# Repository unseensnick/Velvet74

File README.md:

# Velvet74

A 74-key split keyboard with Choc switches and a chip-down RP2040 on each half, in the Sofle layout. Key positions,
the board outline and the case come from [Ergogen](https://github.com/ergogen/ergogen); parts, nets and
fabrication data live in a KiCad 10 project aimed at JLCPCB assembly.

## The board

One 4-layer board, 268 x 118 mm before the panel rails, holds both halves 10 mm apart. Each half has 37 keys: a 6 x 5 matrix, 5 thumb
keys and 2 EC11 encoders that double as keys, each with an SK6812MINI-E under it.

- **Controller (per half):** RP2040, W25Q128JV 16 MB QSPI flash, 12 MHz ABM8-272-T3 crystal, AP2112K-3.3 LDO,
  BOOTSEL and RESET buttons.
- **USB-C host port:** 1.1 A polyfuse, B5819W reverse-current diode into +5V, SMF5.0A TVS on VBUS, USBLC6-2P6 on
  the data pair.
- **USB-C link port:** joins the halves (+5V, ground and a one-wire link on GP12), protected by its own USBLC6-2P6.
- **Display:** a 0.91" SSD1306 module on the 4-pin J3 header (I2C1).
- **Stackup:** signals on F.Cu and B.Cu, the +5V plane on In1 (with a +3.3V island under the controller), GND on
  In2. Power runs through the planes.
- **Panel:** the halves ship as one 268 x 131 mm panel. A 5 mm rail above and below carries the 2 mm tooling holes
  and three fiducials, and ten 5 mm tabs hold the halves, five per half, away from the USB-C cutouts. Mouse bites
  perforate each tab at the board edge: snap the tabs, then file the nubs flat. Nothing is left on the keyboard.

The schematic draws one half (`velvet74-half.kicad_sch`) and uses it twice, as sheets `Left` and `Right`.
Left references are plain (U1, SW10); right ones add 200 (U201, SW210). Both halves share one pin map.

## Pin map (both halves)

| Function | Pins |
| --- | --- |
| Rows 1-5, thumb row | GP5, GP4, GP3, GP2, GP1, GP0 |
| Columns outer to inner | GP29, GP28, GP27, GP26, GP25, GP24 |
| Encoder 1 (SW16) | A GP13, B GP14, key column GP20 |
| Encoder 2 (SW65) | A GP18, B GP19 |
| Display I2C1 | SDA GP6, SCL GP7 |
| RGB data | GP10, through the U6 level shifter to 5 V |
| Split link | GP12 |
| VBUS sense | GP9 (10k/10k divider) |
| Handedness jumper JP1 | GP8 (3.3 V = left, GND = right) |

37 LEDs at full white exceed the USB budget, so firmware should cap RGB brightness (around 120 of 255).

## Layout

- `velvet74.kicad_pro` / `.kicad_sch` / `.kicad_pcb` / `.kicad_dru`: the KiCad project, with the half sheet
  above.
- `lib/`: project symbols, footprints and 3D models (`my-soffle.*`), and the used JLCPCB library parts (`jlcpcb/`).
- `datasheets/`: manufacturer datasheets for every part on the board, synced from LCSC.
- `ergogen/`: the live layout (`config.yaml`). `npm run build` writes both halves' points, outline and case to
  `ergogen/output/`.
- `scripts/`: KiCad Python scripts that place parts from the Ergogen points and snap LEDs, diodes and caps to their
  switches.
- `templates/rp2040-inner-column/`: the RP2040 module the controller block started from, with its own README.
- `production/`: fabrication outputs, regenerated from the board before an order. `jlcpcb/` holds the
  Fabrication Toolkit set; `pcbway/` holds a `kicad-cli` set with a manufacturer-part-number BOM and assembly
  drawings. The two placement files use different rotation conventions, so do not mix them (see
  `production/pcbway/README.md`).

`CLAUDE.md` has the detailed file map, the rules for editing the design safely, and the checks.

## Getting started

**To open, review or edit the design** you need only [KiCad 10](https://www.kicad.org/download/) (made with
10.0.3); open `velvet74.kicad_pro`. Every library part the design uses is in the repo: the project's own parts
in `lib/my-soffle.*`, and the JLCPCB parts it uses in `lib/jlcpcb/` (copied from the JLCPCB library, MIT). The
remaining parts and 3D models are KiCad's stock ones. No Plugin and Content Manager packages, environment variables
or library setup are needed, and the 3D viewer shows every part. KiCad 8 cannot open these files; tag
`kicad8-final` is the last KiCad 8 state.

**To regenerate the layout** (key positions, outline, case): [Node.js](https://nodejs.org/) 18 or newer (Ergogen's `mathjs` dependency
requires it), then

```bash
cd ergogen && npm install && npm run build
```

Ergogen 4.2.1 is pinned in `ergogen/package.json`; the output lands in `ergogen/output/`.

**To run the scripts in `scripts/`:** KiCad's bundled Python (`<KiCad>/10.0/bin/python.exe` on Windows), with KiCad
closed. Each script's docstring says how to run it and what it overwrites.

**To regenerate `production/jlcpcb/`:** the Fabrication Toolkit plugin (from the KiCad Plugin and Content
Manager), with its automatic translation left **off**. JLCPCB's zero degrees is the part's orientation in its own
LCSC package drawing, which differs from KiCad's for some packages, so each affected part carries an
`FT Rotation Offset` or `FT Position Offset` field checked against JLC's own footprint. The plugin's name-matching
rules would rotate parts that are already right.

**To regenerate `production/pcbway/`:** `scripts/export_pcbway.py`, which drives `kicad-cli` and then writes the
placement file and an MPN-keyed BOM. Those offset fields are JLCPCB's and must not be applied here, so the
placement file keeps KiCad's own angles; the only correction is moving the four USB-C rows onto the part centroid.

**To commit:** activate the tracked commit-message hook once per clone with `git config core.hooksPath .githooks`
(see `CLAUDE.md` for the message format).

## Checks

```bash
kicad-cli sch erc --severity-error --exit-code-violations velvet74.kicad_sch
kicad-cli pcb drc --schematic-parity --severity-error --exit-code-violations velvet74.kicad_pcb
```

Expected: ERC has no errors. DRC has 26 known `courtyards_overlap` errors (mounting holes H1-H5 against their
neighbouring switches, 13 per half) and no unconnected items or parity issues. With all severities shown there are
also known warnings: 24 ERC `pin_to_pin` warnings and 3 `lib_symbol_mismatch` (J201, J202 and JP201 differ from their
library copies), and DRC silkscreen and `lib_footprint_mismatch` warnings for parts edited on the board.

## License

The design files, scripts and documentation are released under the MIT license (see `LICENSE`): you may use,
modify, build and sell them as long as the copyright notice is kept. The design comes with no warranty; check it
yourself before ordering boards.

Credits and third-party parts:

- The layout follows the [Sofle keyboard](https://github.com/josefadamcik/SofleKeyboard) by Josef Adamcik
  (MIT, (c) 2019 Josef Adamcik).
- `lib/jlcpcb/` holds parts of [CDFER/JLCPCB-Kicad-Library](https://github.com/CDFER/JLCPCB-Kicad-Library)
  (MIT, (c) 2024 Chris Dirks, license in `lib/jlcpcb/LICENSE`).
- `lib/my-soffle.3dshapes/SW_Hotswap_Kailh_Choc_V1.wrl` and the Choc hotswap footprints derive from
  [kiswitch/keyswitch-kicad-library](https://github.com/kiswitch/keyswitch-kicad-library) (MIT and CC-BY-SA 4.0).
- `datasheets/` holds the manufacturers' datasheets. They are the manufacturers' copyright, included for reference
  only, and are not covered by this project's license.

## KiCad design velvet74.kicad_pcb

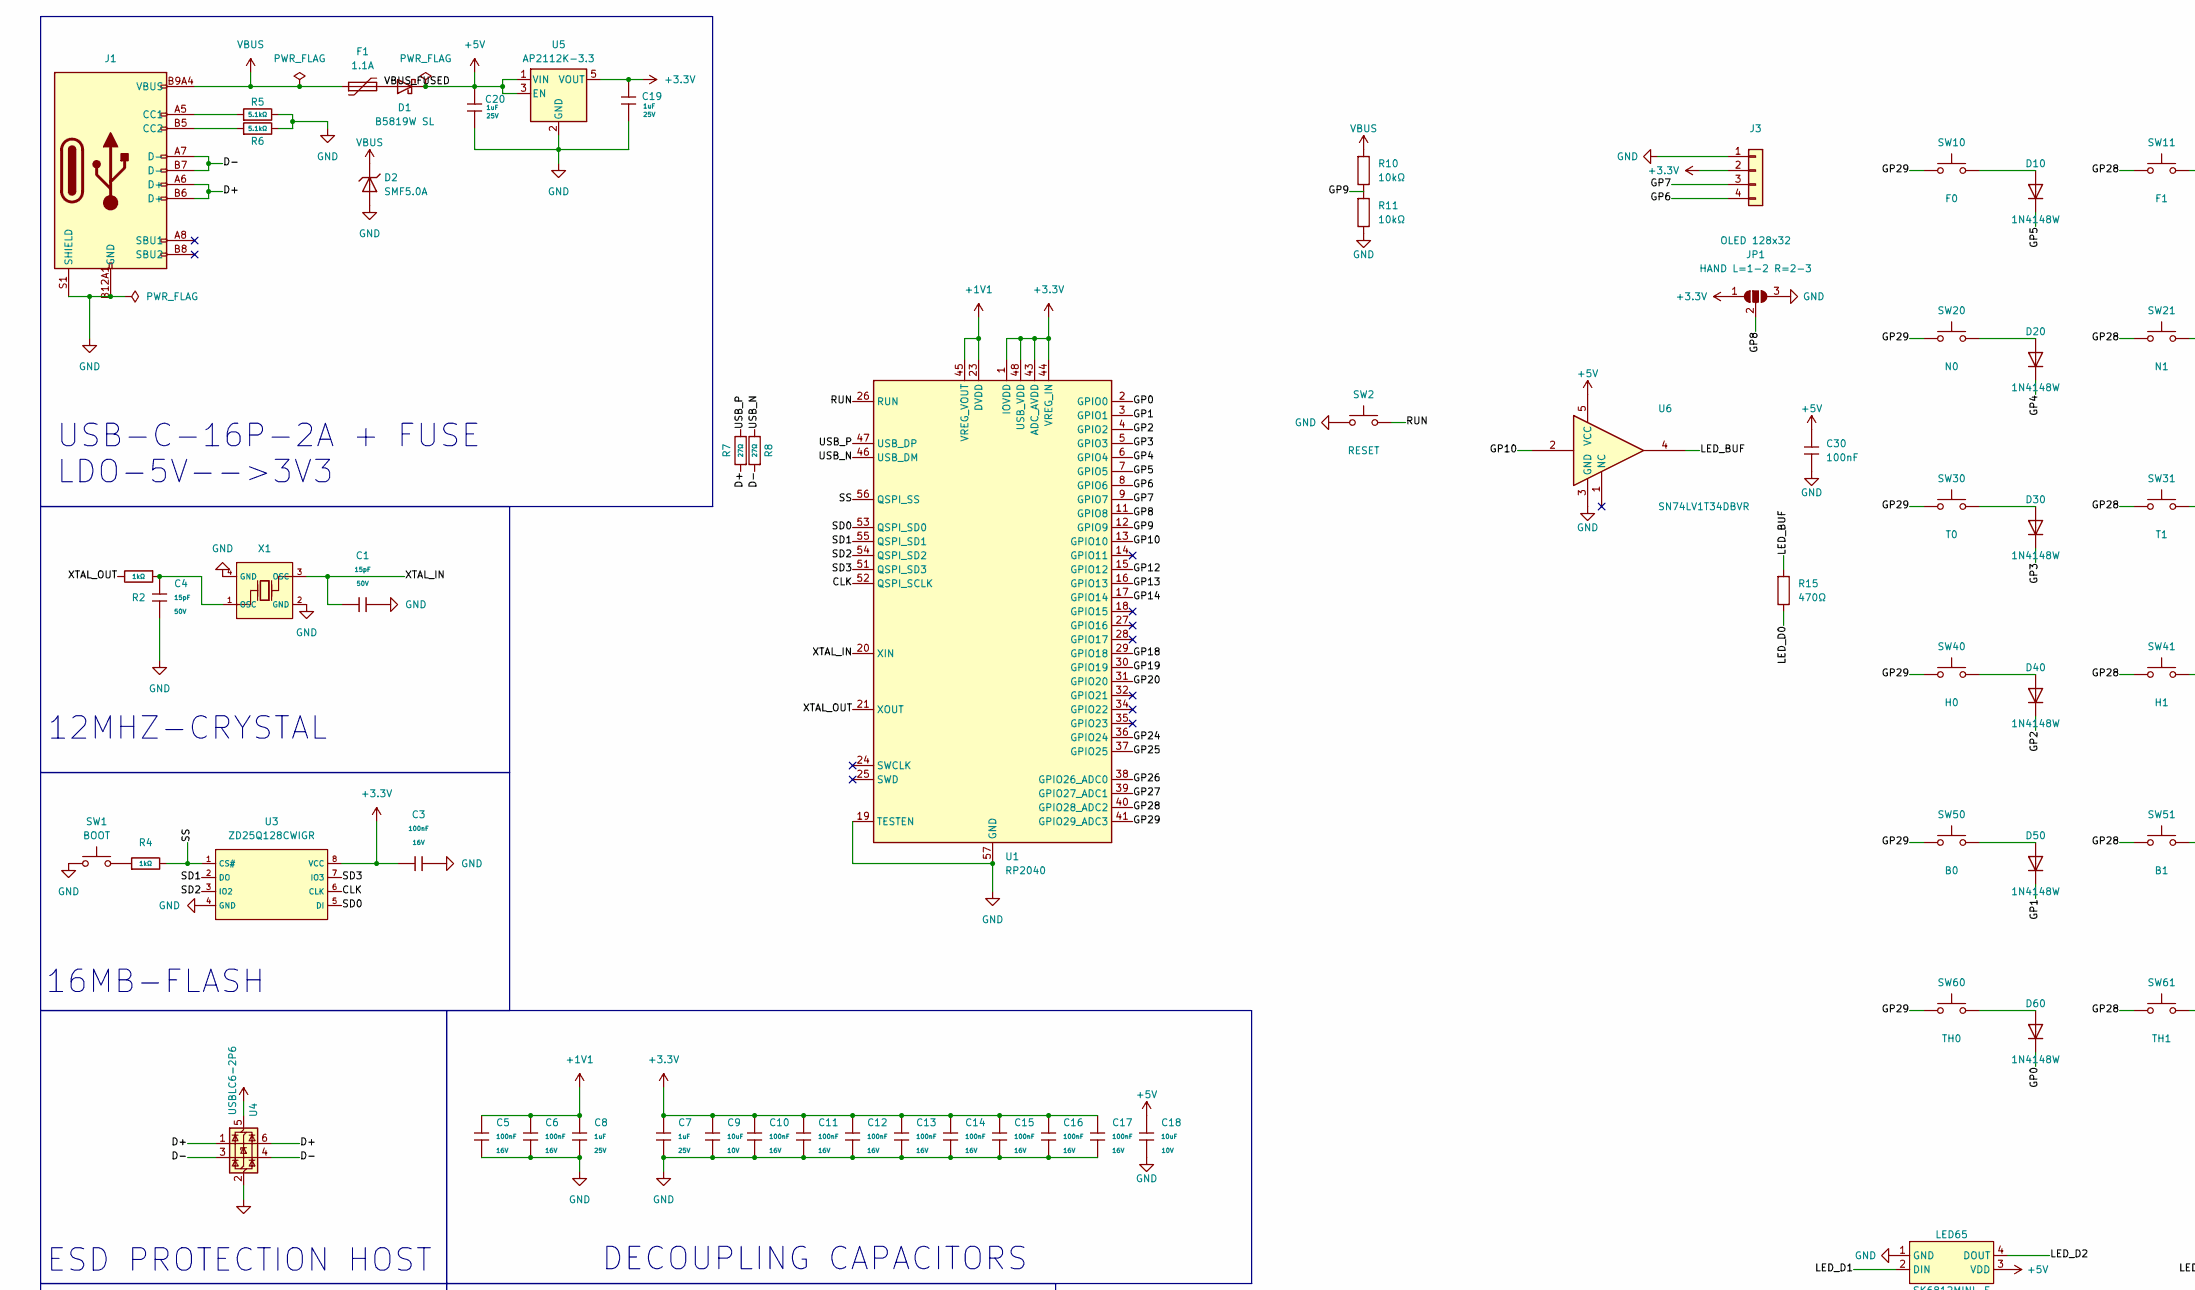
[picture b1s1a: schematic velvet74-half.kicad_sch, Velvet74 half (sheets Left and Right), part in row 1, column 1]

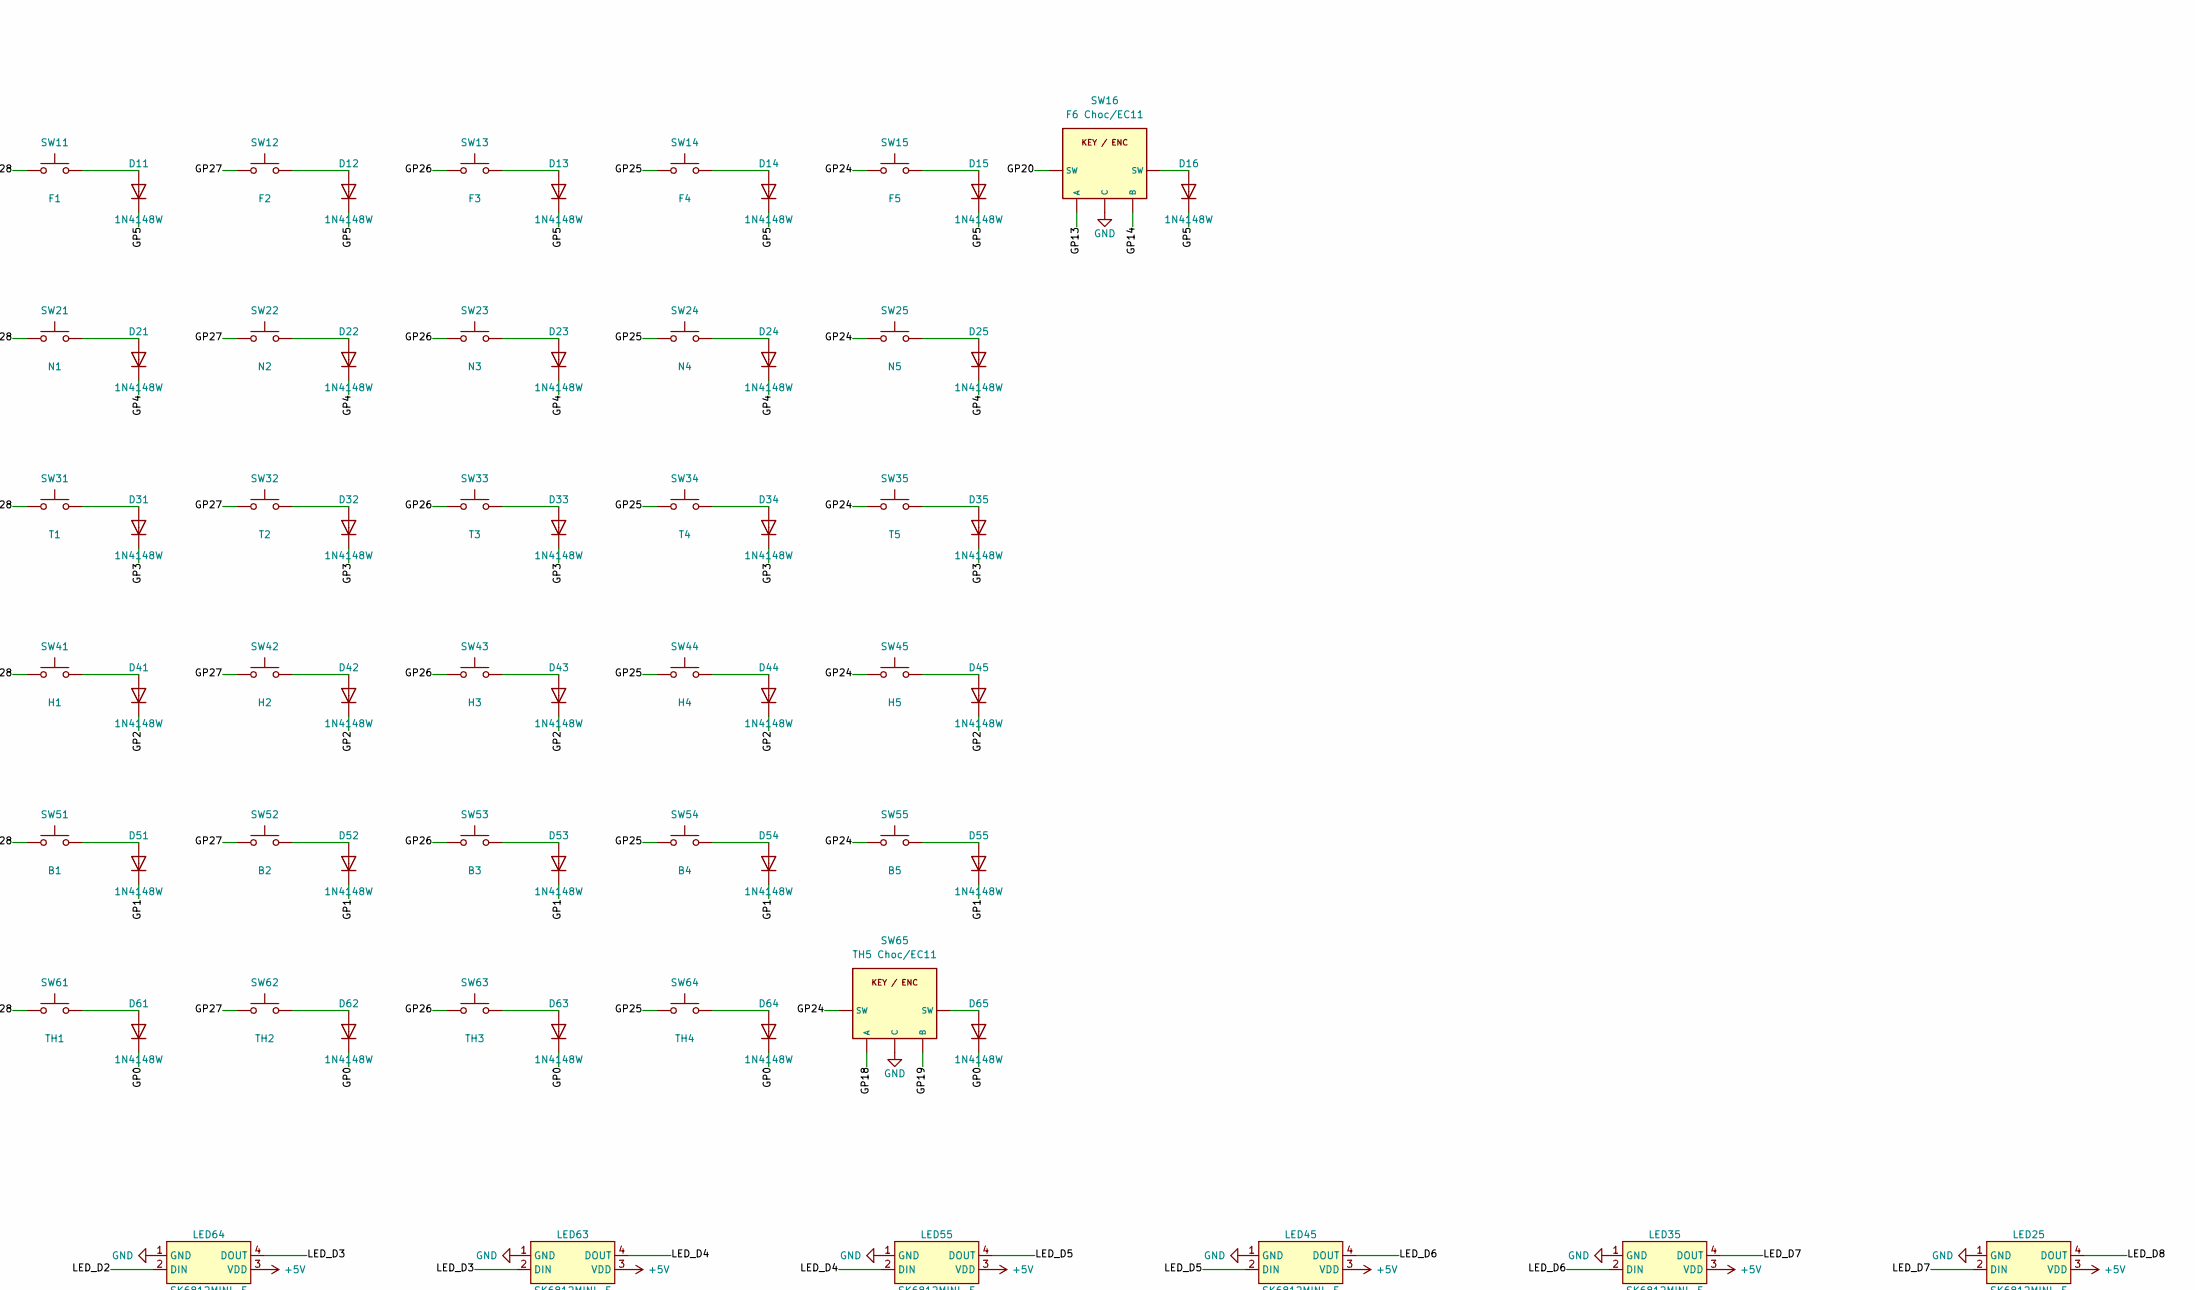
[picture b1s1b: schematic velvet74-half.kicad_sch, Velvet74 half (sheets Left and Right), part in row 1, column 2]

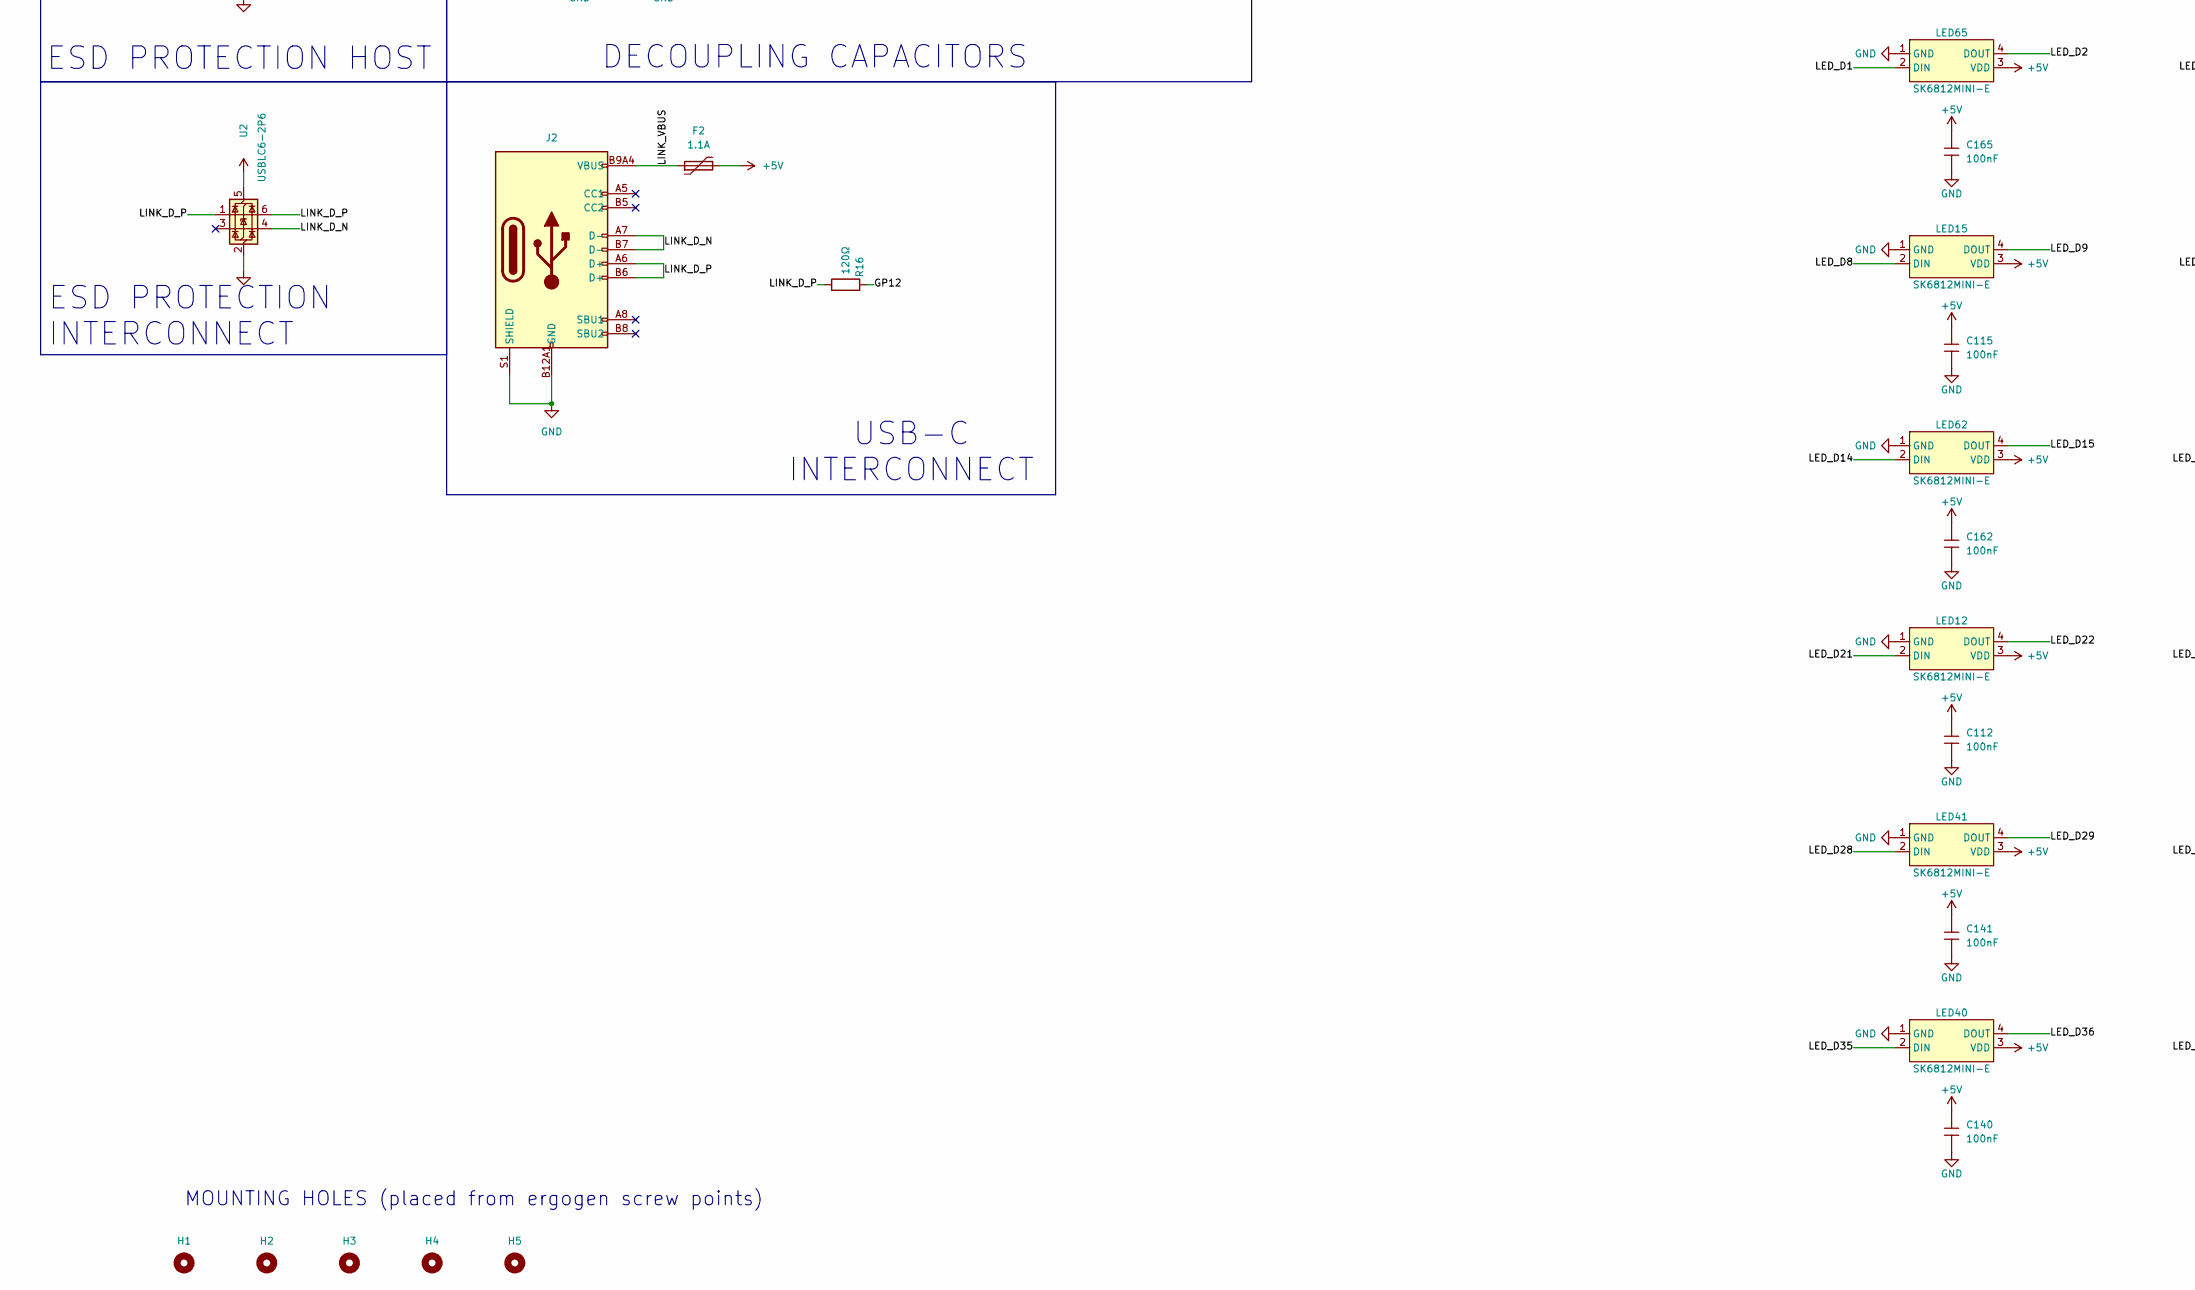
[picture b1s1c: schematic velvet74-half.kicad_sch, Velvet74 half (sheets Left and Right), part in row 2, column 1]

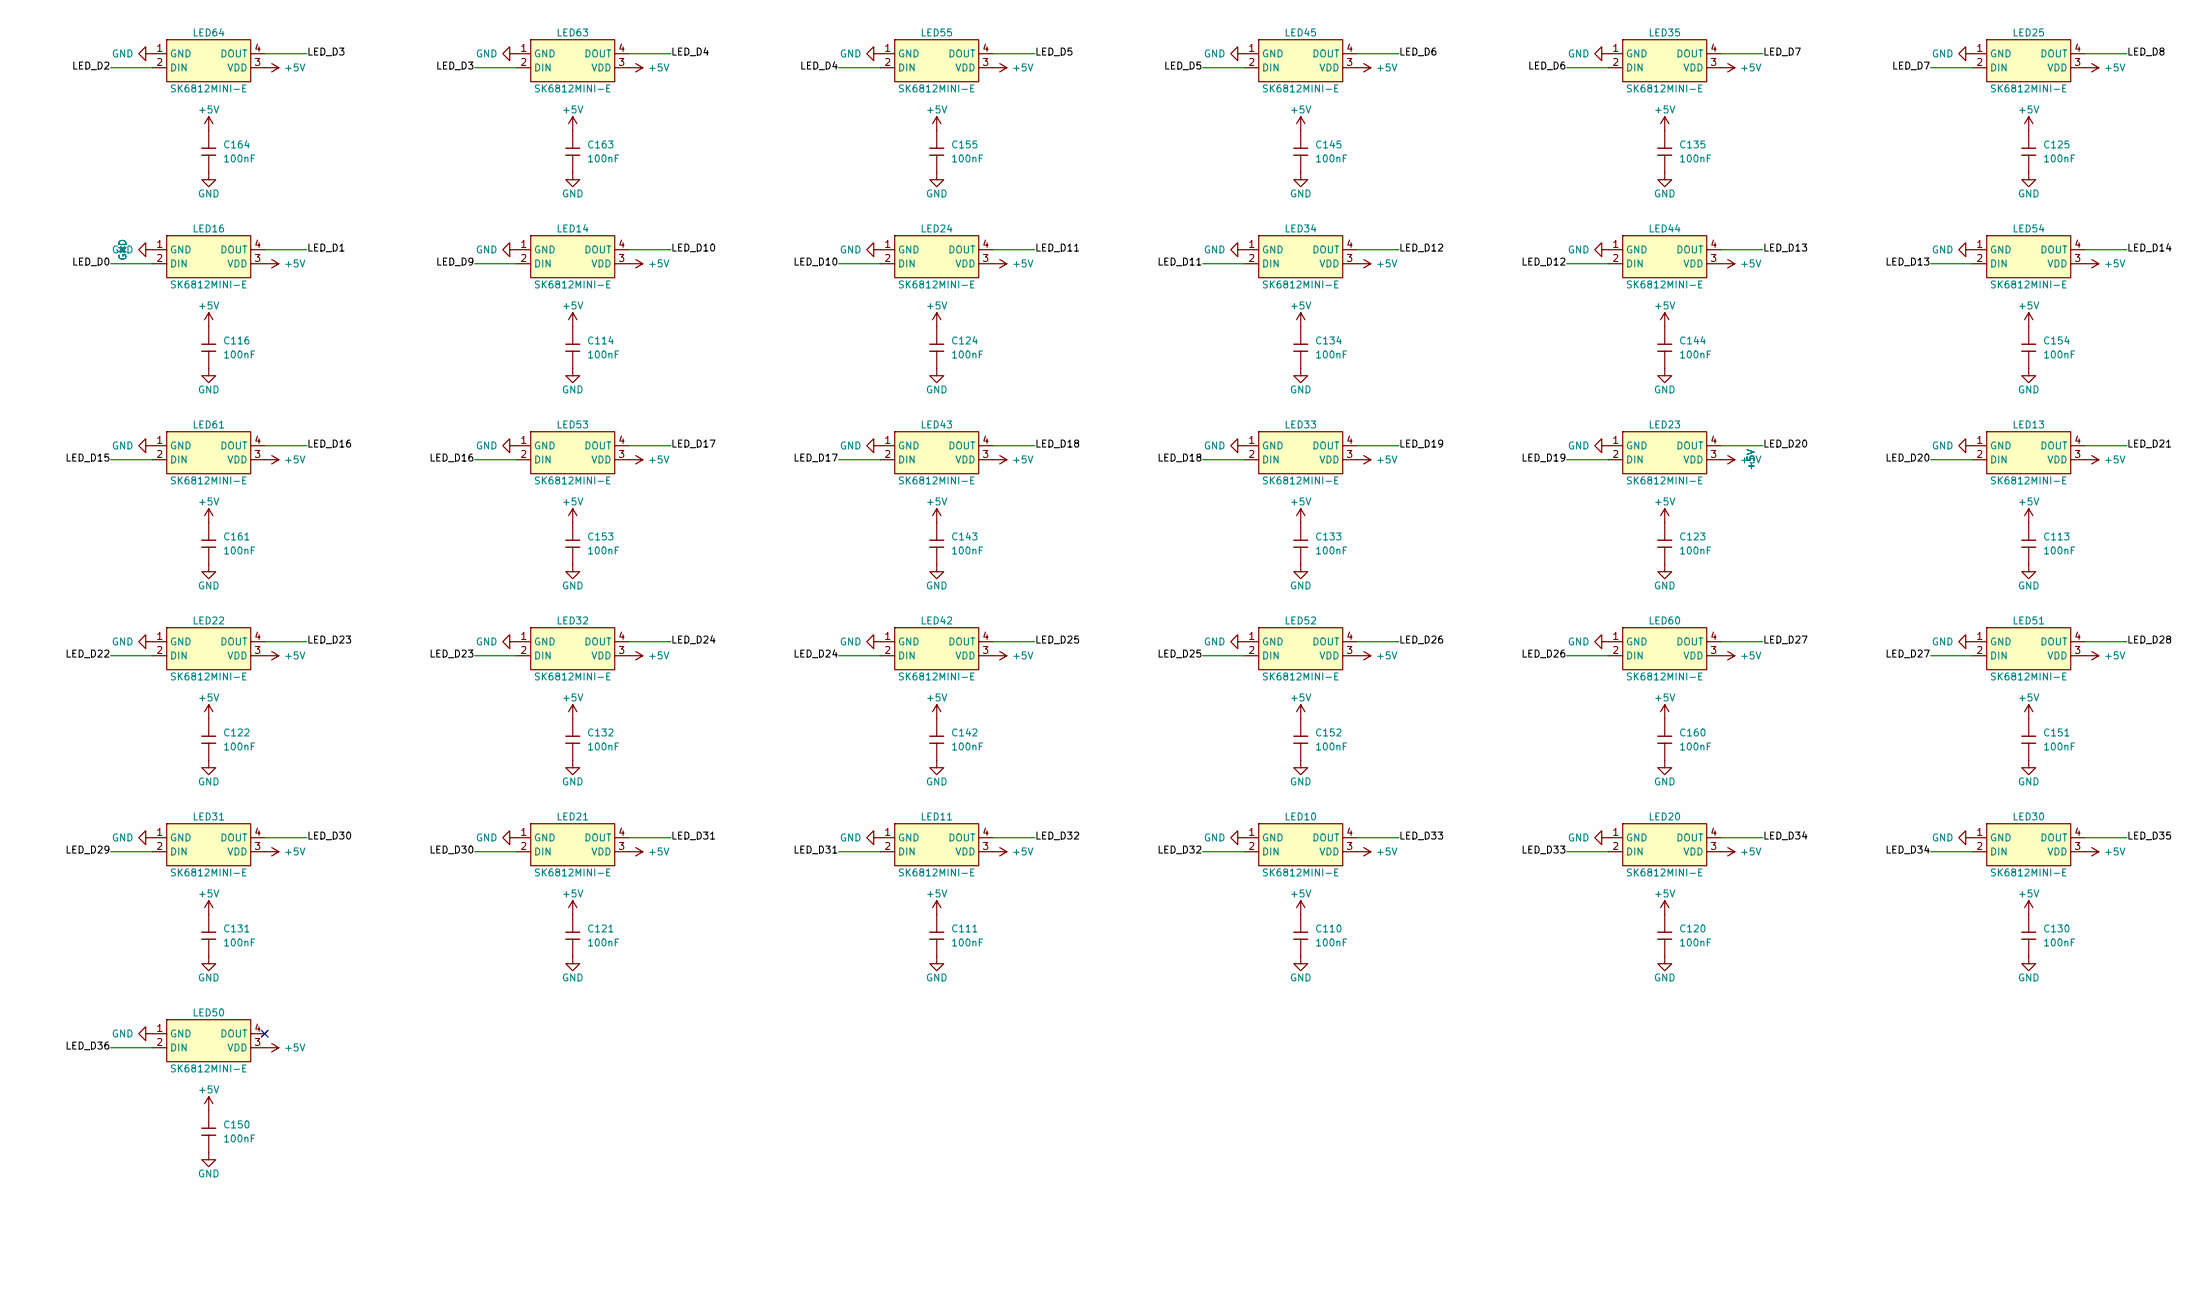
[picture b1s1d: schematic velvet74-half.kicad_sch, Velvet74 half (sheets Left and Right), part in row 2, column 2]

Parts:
C1, C4: 15pF; C_0402; Voltage Rated 50V; Tolerance ±5%; Part 0402CG150J500NT; LCSC C1548
C3, C5, C6, C10, C11, C12, C13, C14, C15, C16, C17, C30, C110, C111, C112, C113, C114, C115, C116, C120, C121, C122, C123, C124, C125, C130, C131, C132, C133, C134, C135, C140, C141, C142, C143, C144, C145, C150, C151, C152, C153, C154, C155, C160, C161, C162, C163, C164, C165: 100nF; C_0402; Voltage Rated 16V; Tolerance ±10%; Part CL05B104KO5NNNC; LCSC C1525
C7, C8, C19, C20: 1uF; C_0402; Voltage Rated 25V; Tolerance ±10%; Part CL05A105KA5NQNC; LCSC C52923
C9: 10uF; C_0603; Voltage Rated 10V; Tolerance ±10%; Part CL10A106KP8NNNC; LCSC C19702
C18: 10uF; C_0603; Voltage Rated 10V; Part CL10A106KP8NNNC; LCSC C19702
D1: B5819W SL; D_SOD-123; Forward Voltage (Vf@If) 600mV@1A; Reverse Voltage (Vr) 40V; Part B5819W SL; LCSC C8598
D2: SMF5.0A; D_SOD-123FL; Part SMF5.0A; LCSC C19077497
D10, D11, D12, D13, D14, D15, D16, D20, D21, D22, D23, D24, D25, D30, D31, D32, D33, D34, D35, D40, D41, D42, D43, D44, D45, D50, D51, D52, D53, D54, D55, D60, D61, D62, D63, D64, D65: 1N4148W; D_SOD-123; Forward Voltage (Vf@If) 1V@50mA; Reverse Voltage (Vr) 75V; Part 1N4148W; LCSC C81598
F1, F2: 1.1A; Fuse_1206_3216Metric; Part 1206L110THYR; LCSC C126818
H1, H2, H3, H4, H5: MountingHole; MountingHole_2.2mm_M2
J1, J2: Connector, USB-TYPE-C-16P; USB_C_Receptacle_HongCheng_HC-TYPE-C-16P_MidMount; LCSC C19274022
J3: OLED 128x32; PinHeader_1x04_P2.54mm_Vertical
JP1: HAND L=1-2 R=2-3; SolderJumper-3_P1.3mm_Open_RoundedPad1.0x1.5mm_NumberLabels
LED10, LED11, LED12, LED13, LED14, LED15, LED16, LED20, LED21, LED22, LED23, LED24, LED25, LED30, LED31, LED32, LED33, LED34, LED35, LED40, LED41, LED42, LED43, LED44, LED45, LED50, LED51, LED52, LED53, LED54, LED55, LED60, LED61, LED62, LED63, LED64, LED65: SK6812MINI-E; LED-SMD_4P-L3.2-W2.8-LS5.9_SK6812MINI-E; MPN SK6812MINI-E; LCSC Part C5149201
R2, R4: 1kΩ; R_0402; Overload Voltage (Max) 50V; Tolerance ±1%; Part 0402WGF1001TCE; LCSC C11702
R5, R6: 5.1kΩ; R_0402; Part 0402WGF5101TCE; LCSC C25905
R7, R8: 27Ω; R_0402; Part 0402WGF270JTCE; LCSC C25100
R10, R11: 10kΩ; R_0402; Overload Voltage (Max) 50V; Tolerance ±1%; Part 0402WGF1002TCE; LCSC C25744
R15: 470Ω; R_0402; Overload Voltage (Max) 50V; Tolerance ±1%; Part 0402WGF4700TCE; LCSC C25117
R16: 120Ω; R_0402; Overload Voltage (Max) 50V; Tolerance ±1%; Part 0402WGF1200TCE; LCSC C25079
SW1: BOOT; SW_Push_1P1T_XUNPU_TS-1088-AR02016; Part TS-1088-AR02016; LCSC C720477
SW2: RESET; SW_Push_1P1T_XUNPU_TS-1088-AR02016; Part TS-1088-AR02016; LCSC C720477
SW10: F0; SW_Choc_V1V2_Hotswap_1.00u
SW11: F1; SW_Choc_V1V2_Hotswap_1.00u
SW12: F2; SW_Choc_V1V2_Hotswap_1.00u
SW13: F3; SW_Choc_V1V2_Hotswap_1.00u
SW14: F4; SW_Choc_V1V2_Hotswap_1.00u
SW15: F5; SW_Choc_V1V2_Hotswap_1.00u
SW16: F6 Choc/EC11; SW_Choc_V1V2_Hotswap_EC11_Combo
SW20: N0; SW_Choc_V1V2_Hotswap_1.00u
SW21: N1; SW_Choc_V1V2_Hotswap_1.00u
SW22: N2; SW_Choc_V1V2_Hotswap_1.00u
SW23: N3; SW_Choc_V1V2_Hotswap_1.00u
SW24: N4; SW_Choc_V1V2_Hotswap_1.00u
SW25: N5; SW_Choc_V1V2_Hotswap_1.00u
SW30: T0; SW_Choc_V1V2_Hotswap_1.00u
SW31: T1; SW_Choc_V1V2_Hotswap_1.00u
SW32: T2; SW_Choc_V1V2_Hotswap_1.00u
SW33: T3; SW_Choc_V1V2_Hotswap_1.00u
SW34: T4; SW_Choc_V1V2_Hotswap_1.00u
SW35: T5; SW_Choc_V1V2_Hotswap_1.00u
SW40: H0; SW_Choc_V1V2_Hotswap_1.00u
SW41: H1; SW_Choc_V1V2_Hotswap_1.00u
SW42: H2; SW_Choc_V1V2_Hotswap_1.00u
SW43: H3; SW_Choc_V1V2_Hotswap_1.00u
SW44: H4; SW_Choc_V1V2_Hotswap_1.00u
SW45: H5; SW_Choc_V1V2_Hotswap_1.00u
SW50: B0; SW_Choc_V1V2_Hotswap_1.00u
SW51: B1; SW_Choc_V1V2_Hotswap_1.00u
SW52: B2; SW_Choc_V1V2_Hotswap_1.00u
SW53: B3; SW_Choc_V1V2_Hotswap_1.00u
SW54: B4; SW_Choc_V1V2_Hotswap_1.00u
SW55: B5; SW_Choc_V1V2_Hotswap_1.00u
SW60: TH0; SW_Choc_V1V2_Hotswap_1.00u
SW61: TH1; SW_Choc_V1V2_Hotswap_1.00u
SW62: TH2; SW_Choc_V1V2_Hotswap_1.00u
SW63: TH3; SW_Choc_V1V2_Hotswap_1.00u
SW64: TH4; SW_Choc_V1V2_Hotswap_1.50u
SW65: TH5 Choc/EC11; SW_Choc_V1V2_Hotswap_EC11_Combo
U1: RP2040; QFN-56-1EP_7x7mm_P0.4mm_EP3.2x3.2mm_ThermalVias; LCSC C2040
U2, U4: USBLC6-2P6; SOT-563_USBLC6-2P6; Part USBLC6-2P6; LCSC C49451919
U3: ZD25Q128CWIGR; WSON-8-1EP_6x5mm_P1.27mm_EP3.4x4mm; Part ZD25Q128CWIGR; LCSC C53959302
U5: AP2112K-3.3; SOT-23-5_L3.0-W1.7-P0.95-LS2.8-BL; Part AP2112K-3.3TRG1; LCSC C51118
U6: SN74LV1T34DBVR; SOT-23-5; LCSC C100024
X1: ABM8-272-T3; CRYSTAL-SMD_4P-L3.2-W2.5-BL; Frequency Tolerance ±30ppm; Part ABM8-272-T3; LCSC C20625731

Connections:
/Left/+1V1: C5.1, C6.1, C8.1, U1.23 (DVDD), U1.45 (VREG_VOUT), U1.50 (DVDD)
/Left/+3.3V: C3.1, C7.1, C9.1, C10.1, C11.1, C12.1, C13.1, C14.1, C15.1, C16.1, C17.1, C19.1, J3.2, JP1.1 (A), U1.1 (IOVDD), U1.10 (IOVDD), U1.22 (IOVDD), U1.33 (IOVDD), U1.42 (IOVDD), U1.43 (ADC_AVDD), U1.44 (VREG_IN), U1.48 (USB_VDD), U1.49 (IOVDD), U3.8 (VCC), U5.5 (VOUT)
/Left/+5V: C18.1, C20.1, C30.1, C110.1, C111.1, C112.1, C113.1, C114.1, C115.1, C116.1, C120.1, C121.1, C122.1, C123.1, C124.1, C125.1, C130.1, C131.1, C132.1, C133.1, C134.1, C135.1, C140.1, C141.1, C142.1, C143.1, C144.1, C145.1, C150.1, C151.1, C152.1, C153.1, C154.1, C155.1, C160.1, C161.1, C162.1, C163.1, C164.1, C165.1, D1.1, F2.2, LED10.3 (VDD), LED11.3 (VDD), LED12.3 (VDD), LED13.3 (VDD), LED14.3 (VDD), LED15.3 (VDD), LED16.3 (VDD), LED20.3 (VDD), LED21.3 (VDD), LED22.3 (VDD), LED23.3 (VDD), LED24.3 (VDD), LED25.3 (VDD), LED30.3 (VDD), LED31.3 (VDD), LED32.3 (VDD), LED33.3 (VDD), LED34.3 (VDD), LED35.3 (VDD), LED40.3 (VDD), LED41.3 (VDD), LED42.3 (VDD), LED43.3 (VDD), LED44.3 (VDD), LED45.3 (VDD), LED50.3 (VDD), LED51.3 (VDD), LED52.3 (VDD), LED53.3 (VDD), LED54.3 (VDD), LED55.3 (VDD), LED60.3 (VDD), LED61.3 (VDD), LED62.3 (VDD), LED63.3 (VDD), LED64.3 (VDD), LED65.3 (VDD), U2.5 (VBUS), U4.5 (VBUS), U5.1 (VIN), U5.3 (EN), U6.5 (VCC)
/Left/CLK: U1.52 (QSPI_SCLK), U3.6 (CLK)
/Left/D+: J1.A6 (D+), J1.B6 (D+), R7.1, U4.1 (I/O1), U4.6 (I/O1)
/Left/D-: J1.A7 (D-), J1.B7 (D-), R8.1, U4.3 (I/O2), U4.4 (I/O2)
/Left/GND: C1.1, C3.2, C4.1, C5.2, C6.2, C7.2, C8.2, C9.2, C10.2, C11.2, C12.2, C13.2, C14.2, C15.2, C16.2, C17.2, C18.2, C19.2, C20.2, C30.2, C110.2, C111.2, C112.2, C113.2, C114.2, C115.2, C116.2, C120.2, C121.2, C122.2, C123.2, C124.2, C125.2, C130.2, C131.2, C132.2, C133.2, C134.2, C135.2, C140.2, C141.2, C142.2, C143.2, C144.2, C145.2, C150.2, C151.2, C152.2, C153.2, C154.2, C155.2, C160.2, C161.2, C162.2, C163.2, C164.2, C165.2, D2.2, J1.A12B1 (GND), J1.B12A1 (GND), J1.S1 (SHIELD), J2.A12B1 (GND), J2.B12A1 (GND), J2.S1 (SHIELD), J3.1, JP1.3 (B), LED10.1 (GND), LED11.1 (GND), LED12.1 (GND), LED13.1 (GND), LED14.1 (GND), LED15.1 (GND), LED16.1 (GND), LED20.1 (GND), LED21.1 (GND), LED22.1 (GND), LED23.1 (GND), LED24.1 (GND), LED25.1 (GND), LED30.1 (GND), LED31.1 (GND), LED32.1 (GND), LED33.1 (GND), LED34.1 (GND), LED35.1 (GND), LED40.1 (GND), LED41.1 (GND), LED42.1 (GND), LED43.1 (GND), LED44.1 (GND), LED45.1 (GND), LED50.1 (GND), LED51.1 (GND), LED52.1 (GND), LED53.1 (GND), LED54.1 (GND), LED55.1 (GND), LED60.1 (GND), LED61.1 (GND), LED62.1 (GND), LED63.1 (GND), LED64.1 (GND), LED65.1 (GND), R5.2, R6.2, R11.2, SW1.1, SW2.1, SW16.C, SW65.C, U1.19 (TESTEN), U1.57 (GND), U2.2 (GND), U3.4 (GND), U4.2 (GND), U5.2 (GND), U6.3 (GND), X1.2 (GND), X1.4 (GND)
/Left/GP0: D60.1, D61.1, D62.1, D63.1, D64.1, D65.1, U1.2 (GPIO0)
/Left/GP1: D50.1, D51.1, D52.1, D53.1, D54.1, D55.1, U1.3 (GPIO1)
/Left/GP2: D40.1, D41.1, D42.1, D43.1, D44.1, D45.1, U1.4 (GPIO2)
/Left/GP3: D30.1, D31.1, D32.1, D33.1, D34.1, D35.1, U1.5 (GPIO3)
/Left/GP4: D20.1, D21.1, D22.1, D23.1, D24.1, D25.1, U1.6 (GPIO4)
/Left/GP5: D10.1, D11.1, D12.1, D13.1, D14.1, D15.1, D16.1, U1.7 (GPIO5)
/Left/GP6: J3.4, U1.8 (GPIO6)
/Left/GP7: J3.3, U1.9 (GPIO7)
/Left/GP8: JP1.2 (C), U1.11 (GPIO8)
/Left/GP9: R10.2, R11.1, U1.12 (GPIO9)
/Left/GP10: U1.13 (GPIO10), U6.2
/Left/GP12: R16.2, U1.15 (GPIO12)
/Left/GP13: SW16.A, U1.16 (GPIO13)
/Left/GP14: SW16.B, U1.17 (GPIO14)
/Left/GP18: SW65.A, U1.29 (GPIO18)
/Left/GP19: SW65.B, U1.30 (GPIO19)
/Left/GP20: SW16.1 (SW), U1.31 (GPIO20)
/Left/GP24: SW15.1, SW25.1, SW35.1, SW45.1, SW55.1, SW65.1 (SW), U1.36 (GPIO24)
/Left/GP25: SW14.1, SW24.1, SW34.1, SW44.1, SW54.1, SW64.1, U1.37 (GPIO25)
/Left/GP26: SW13.1, SW23.1, SW33.1, SW43.1, SW53.1, SW63.1, U1.38 (GPIO26_ADC0)
/Left/GP27: SW12.1, SW22.1, SW32.1, SW42.1, SW52.1, SW62.1, U1.39 (GPIO27_ADC1)
/Left/GP28: SW11.1, SW21.1, SW31.1, SW41.1, SW51.1, SW61.1, U1.40 (GPIO28_ADC2)
/Left/GP29: SW10.1, SW20.1, SW30.1, SW40.1, SW50.1, SW60.1, U1.41 (GPIO29_ADC3)
/Left/LED_BUF: R15.1, U6.4
/Left/LED_D0: LED16.2 (DIN), R15.2
/Left/LED_D1: LED16.4 (DOUT), LED65.2 (DIN)
/Left/LED_D2: LED64.2 (DIN), LED65.4 (DOUT)
/Left/LED_D3: LED63.2 (DIN), LED64.4 (DOUT)
/Left/LED_D4: LED55.2 (DIN), LED63.4 (DOUT)
/Left/LED_D5: LED45.2 (DIN), LED55.4 (DOUT)
/Left/LED_D6: LED35.2 (DIN), LED45.4 (DOUT)
/Left/LED_D7: LED25.2 (DIN), LED35.4 (DOUT)
/Left/LED_D8: LED15.2 (DIN), LED25.4 (DOUT)
/Left/LED_D9: LED14.2 (DIN), LED15.4 (DOUT)
/Left/LED_D10: LED14.4 (DOUT), LED24.2 (DIN)
/Left/LED_D11: LED24.4 (DOUT), LED34.2 (DIN)
/Left/LED_D12: LED34.4 (DOUT), LED44.2 (DIN)
/Left/LED_D13: LED44.4 (DOUT), LED54.2 (DIN)
/Left/LED_D14: LED54.4 (DOUT), LED62.2 (DIN)
/Left/LED_D15: LED61.2 (DIN), LED62.4 (DOUT)
/Left/LED_D16: LED53.2 (DIN), LED61.4 (DOUT)
/Left/LED_D17: LED43.2 (DIN), LED53.4 (DOUT)
/Left/LED_D18: LED33.2 (DIN), LED43.4 (DOUT)
/Left/LED_D19: LED23.2 (DIN), LED33.4 (DOUT)
/Left/LED_D20: LED13.2 (DIN), LED23.4 (DOUT)
/Left/LED_D21: LED12.2 (DIN), LED13.4 (DOUT)
/Left/LED_D22: LED12.4 (DOUT), LED22.2 (DIN)
/Left/LED_D23: LED22.4 (DOUT), LED32.2 (DIN)
/Left/LED_D24: LED32.4 (DOUT), LED42.2 (DIN)
/Left/LED_D25: LED42.4 (DOUT), LED52.2 (DIN)
/Left/LED_D26: LED52.4 (DOUT), LED60.2 (DIN)
/Left/LED_D27: LED51.2 (DIN), LED60.4 (DOUT)
/Left/LED_D28: LED41.2 (DIN), LED51.4 (DOUT)
/Left/LED_D29: LED31.2 (DIN), LED41.4 (DOUT)
/Left/LED_D30: LED21.2 (DIN), LED31.4 (DOUT)
/Left/LED_D31: LED11.2 (DIN), LED21.4 (DOUT)
/Left/LED_D32: LED10.2 (DIN), LED11.4 (DOUT)
/Left/LED_D33: LED10.4 (DOUT), LED20.2 (DIN)
/Left/LED_D34: LED20.4 (DOUT), LED30.2 (DIN)
/Left/LED_D35: LED30.4 (DOUT), LED40.2 (DIN)
/Left/LED_D36: LED40.4 (DOUT), LED50.2 (DIN)
/Left/LINK_D_N: J2.A7 (D-), J2.B7 (D-), U2.4 (I/O2)
/Left/LINK_D_P: J2.A6 (D+), J2.B6 (D+), R16.1, U2.1 (I/O1), U2.6 (I/O1)
/Left/LINK_VBUS: F2.1, J2.A9B4 (VBUS), J2.B9A4 (VBUS)
/Left/RUN: SW2.2, U1.26 (RUN)
/Left/SD0: U1.53 (QSPI_SD0), U3.5 (DI)
/Left/SD1: U1.55 (QSPI_SD1), U3.2 (DO)
/Left/SD2: U1.54 (QSPI_SD2), U3.3 (IO2)
/Left/SD3: U1.51 (QSPI_SD3), U3.7 (IO3)
/Left/SS: R4.2, U1.56 (QSPI_SS), U3.1 (CS#)
/Left/USB_N: R8.2, U1.46 (USB_DM)
/Left/USB_P: R7.2, U1.47 (USB_DP)
/Left/VBUS: D2.1, F1.1, J1.A9B4 (VBUS), J1.B9A4 (VBUS), R10.1
/Left/VBUS_FUSED: D1.2, F1.2
/Left/XTAL_IN: C1.2, U1.20 (XIN), X1.3 (OSC)
/Left/XTAL_OUT: R2.2, U1.21 (XOUT)
unnamed: C4.2, R2.1, X1.1 (OSC)
unnamed: D10.2, SW10.2
unnamed: D11.2, SW11.2
unnamed: D12.2, SW12.2
unnamed: D13.2, SW13.2
unnamed: D14.2, SW14.2
unnamed: D15.2, SW15.2
unnamed: D16.2, SW16.2 (SW)
unnamed: D20.2, SW20.2
unnamed: D21.2, SW21.2
unnamed: D22.2, SW22.2
unnamed: D23.2, SW23.2
unnamed: D24.2, SW24.2
unnamed: D25.2, SW25.2
unnamed: D30.2, SW30.2
unnamed: D31.2, SW31.2
unnamed: D32.2, SW32.2
unnamed: D33.2, SW33.2
unnamed: D34.2, SW34.2
unnamed: D35.2, SW35.2
unnamed: D40.2, SW40.2
unnamed: D41.2, SW41.2
unnamed: D42.2, SW42.2
unnamed: D43.2, SW43.2
unnamed: D44.2, SW44.2
unnamed: D45.2, SW45.2
unnamed: D50.2, SW50.2
unnamed: D51.2, SW51.2
unnamed: D52.2, SW52.2
unnamed: D53.2, SW53.2
unnamed: D54.2, SW54.2
unnamed: D55.2, SW55.2
unnamed: D60.2, SW60.2
unnamed: D61.2, SW61.2
unnamed: D62.2, SW62.2
unnamed: D63.2, SW63.2
unnamed: D64.2, SW64.2
unnamed: D65.2, SW65.2 (SW)
unnamed: J1.A5 (CC1), R5.1
unnamed: J1.B5 (CC2), R6.1
unnamed: R4.1, SW1.2

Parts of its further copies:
C201, C204: 15pF; C_0402; Voltage Rated 50V; Tolerance ±5%; Part 0402CG150J500NT; LCSC C1548
C203, C205, C206, C210, C211, C212, C213, C214, C215, C216, C217, C230, C310, C311, C312, C313, C314, C315, C316, C320, C321, C322, C323, C324, C325, C330, C331, C332, C333, C334, C335, C340, C341, C342, C343, C344, C345, C350, C351, C352, C353, C354, C355, C360, C361, C362, C363, C364, C365: 100nF; C_0402; Voltage Rated 16V; Tolerance ±10%; Part CL05B104KO5NNNC; LCSC C1525
C207, C208, C219, C220: 1uF; C_0402; Voltage Rated 25V; Tolerance ±10%; Part CL05A105KA5NQNC; LCSC C52923
C209: 10uF; C_0603; Voltage Rated 10V; Tolerance ±10%; Part CL10A106KP8NNNC; LCSC C19702
C218: 10uF; C_0603; Voltage Rated 10V; Part CL10A106KP8NNNC; LCSC C19702
D201: B5819W SL; D_SOD-123; Forward Voltage (Vf@If) 600mV@1A; Reverse Voltage (Vr) 40V; Part B5819W SL; LCSC C8598
D202: SMF5.0A; D_SOD-123FL; Part SMF5.0A; LCSC C19077497
D210, D211, D212, D213, D214, D215, D216, D220, D221, D222, D223, D224, D225, D230, D231, D232, D233, D234, D235, D240, D241, D242, D243, D244, D245, D250, D251, D252, D253, D254, D255, D260, D261, D262, D263, D264, D265: 1N4148W; D_SOD-123; Forward Voltage (Vf@If) 1V@50mA; Reverse Voltage (Vr) 75V; Part 1N4148W; LCSC C81598
F201, F202: 1.1A; Fuse_1206_3216Metric; Part 1206L110THYR; LCSC C126818
H201, H202, H203, H204, H205: MountingHole; MountingHole_2.2mm_M2
J201, J202: Connector, USB-TYPE-C-16P; USB_C_Receptacle_HongCheng_HC-TYPE-C-16P_MidMount; LCSC C19274022
J203: OLED 128x32; PinHeader_1x04_P2.54mm_Vertical
JP201: HAND L=1-2 R=2-3; SolderJumper-3_P1.3mm_Open_RoundedPad1.0x1.5mm_NumberLabels
LED210, LED211, LED212, LED213, LED214, LED215, LED216, LED220, LED221, LED222, LED223, LED224, LED225, LED230, LED231, LED232, LED233, LED234, LED235, LED240, LED241, LED242, LED243, LED244, LED245, LED250, LED251, LED252, LED253, LED254, LED255, LED260, LED261, LED262, LED263, LED264, LED265: SK6812MINI-E; LED-SMD_4P-L3.2-W2.8-LS5.9_SK6812MINI-E; MPN SK6812MINI-E; LCSC Part C5149201
R202, R204: 1kΩ; R_0402; Overload Voltage (Max) 50V; Tolerance ±1%; Part 0402WGF1001TCE; LCSC C11702
R205, R206: 5.1kΩ; R_0402; Part 0402WGF5101TCE; LCSC C25905
R207, R208: 27Ω; R_0402; Part 0402WGF270JTCE; LCSC C25100
R210, R211: 10kΩ; R_0402; Overload Voltage (Max) 50V; Tolerance ±1%; Part 0402WGF1002TCE; LCSC C25744
R215: 470Ω; R_0402; Overload Voltage (Max) 50V; Tolerance ±1%; Part 0402WGF4700TCE; LCSC C25117
R216: 120Ω; R_0402; Overload Voltage (Max) 50V; Tolerance ±1%; Part 0402WGF1200TCE; LCSC C25079
SW201: BOOT; SW_Push_1P1T_XUNPU_TS-1088-AR02016; Part TS-1088-AR02016; LCSC C720477
SW202: RESET; SW_Push_1P1T_XUNPU_TS-1088-AR02016; Part TS-1088-AR02016; LCSC C720477
SW210: F0; SW_Choc_V1V2_Hotswap_1.00u
SW211: F1; SW_Choc_V1V2_Hotswap_1.00u
SW212: F2; SW_Choc_V1V2_Hotswap_1.00u
SW213: F3; SW_Choc_V1V2_Hotswap_1.00u
SW214: F4; SW_Choc_V1V2_Hotswap_1.00u
SW215: F5; SW_Choc_V1V2_Hotswap_1.00u
SW216: F6 Choc/EC11; SW_Choc_V1V2_Hotswap_EC11_Combo
SW220: N0; SW_Choc_V1V2_Hotswap_1.00u
SW221: N1; SW_Choc_V1V2_Hotswap_1.00u
SW222: N2; SW_Choc_V1V2_Hotswap_1.00u
SW223: N3; SW_Choc_V1V2_Hotswap_1.00u
SW224: N4; SW_Choc_V1V2_Hotswap_1.00u
SW225: N5; SW_Choc_V1V2_Hotswap_1.00u
SW230: T0; SW_Choc_V1V2_Hotswap_1.00u
SW231: T1; SW_Choc_V1V2_Hotswap_1.00u
SW232: T2; SW_Choc_V1V2_Hotswap_1.00u
SW233: T3; SW_Choc_V1V2_Hotswap_1.00u
SW234: T4; SW_Choc_V1V2_Hotswap_1.00u
SW235: T5; SW_Choc_V1V2_Hotswap_1.00u
SW240: H0; SW_Choc_V1V2_Hotswap_1.00u
SW241: H1; SW_Choc_V1V2_Hotswap_1.00u
SW242: H2; SW_Choc_V1V2_Hotswap_1.00u
SW243: H3; SW_Choc_V1V2_Hotswap_1.00u
SW244: H4; SW_Choc_V1V2_Hotswap_1.00u
SW245: H5; SW_Choc_V1V2_Hotswap_1.00u
SW250: B0; SW_Choc_V1V2_Hotswap_1.00u
SW251: B1; SW_Choc_V1V2_Hotswap_1.00u
SW252: B2; SW_Choc_V1V2_Hotswap_1.00u
SW253: B3; SW_Choc_V1V2_Hotswap_1.00u
SW254: B4; SW_Choc_V1V2_Hotswap_1.00u
SW255: B5; SW_Choc_V1V2_Hotswap_1.00u
SW260: TH0; SW_Choc_V1V2_Hotswap_1.00u
SW261: TH1; SW_Choc_V1V2_Hotswap_1.00u
SW262: TH2; SW_Choc_V1V2_Hotswap_1.00u
SW263: TH3; SW_Choc_V1V2_Hotswap_1.00u
SW264: TH4; SW_Choc_V1V2_Hotswap_1.50u
SW265: TH5 Choc/EC11; SW_Choc_V1V2_Hotswap_EC11_Combo
U201: RP2040; QFN-56-1EP_7x7mm_P0.4mm_EP3.2x3.2mm_ThermalVias; LCSC C2040
U202, U204: USBLC6-2P6; SOT-563_USBLC6-2P6; Part USBLC6-2P6; LCSC C49451919
U203: ZD25Q128CWIGR; WSON-8-1EP_6x5mm_P1.27mm_EP3.4x4mm; Part ZD25Q128CWIGR; LCSC C53959302
U205: AP2112K-3.3; SOT-23-5_L3.0-W1.7-P0.95-LS2.8-BL; Part AP2112K-3.3TRG1; LCSC C51118
U206: SN74LV1T34DBVR; SOT-23-5; LCSC C100024
X201: ABM8-272-T3; CRYSTAL-SMD_4P-L3.2-W2.5-BL; Frequency Tolerance ±30ppm; Part ABM8-272-T3; LCSC C20625731

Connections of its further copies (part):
/Right/+1V1: C205.1, C206.1, C208.1, U201.23 (DVDD), U201.45 (VREG_VOUT), U201.50 (DVDD)
/Right/+3.3V: C203.1, C207.1, C209.1, C210.1, C211.1, C212.1, C213.1, C214.1, C215.1, C216.1, C217.1, C219.1, J203.2, JP201.1 (A), U201.1 (IOVDD), U201.10 (IOVDD), U201.22 (IOVDD), U201.33 (IOVDD), U201.42 (IOVDD), U201.43 (ADC_AVDD), U201.44 (VREG_IN), U201.48 (USB_VDD), U201.49 (IOVDD), U203.8 (VCC), U205.5 (VOUT)
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
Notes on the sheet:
USB-C-16P-2A + FUSE LDO-5V-->3V3
DECOUPLING CAPACITORS
ESD PROTECTION INTERCONNECT
16MB-FLASH
12MHZ-CRYSTAL
USB-C INTERCONNECT
ESD PROTECTION HOST
MOUNTING HOLES (placed from ergogen screw points)
